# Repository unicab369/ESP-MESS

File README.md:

# What is it?
ESP-MESS is an open-source firmware for ESP8266 and ESP32 microcontrollers, enabling\
rapid IoT prototyping for home automation, smart farming, smart business, and more. 

## Why ESP-Mess? 
Back in 2020 during Covid, I got an opportunity to look back and decide on what I want to do next. I thought about what I liked as a kid so I decided to build a remote control car. During my search for a suitable microcontroller, I stumbled upon the NodeMcu, a development board that house the ESP8266 module. Initially underestimating its capabilities, I soon realized its potential. Since then, my journey has led me to acquire skills in soldering, basic electronics, embedded programming, web development for microcontrollers, PCB design, and various wireless communication technologies.

I am building a Wireless Bridge System that can manage multiple devices using a variety of wireless technologies. The system is designed to be flexible and scalable, allowing it to adapt to different wireless application requirements. My goal is to explore and discover different IoT applications while keeping the cost minimal. To achieve this, I created ESP-MESS.

## Why a Wireless Bridge System (WBSys)?
Because it's cool. It's very cool. Ok, seriously, different wireless technologies have their own unique advantages and disadvantages. For instance, LoRa technology allows devices to communicate with each other over long distances, which is not possible with WiFi or Bluetooth. However, LoRa has a low data rate, which makes it unsuitable for transmitting large amounts of data such as videos or audios. On the other hand, UWB (Ultra Wide Band) technology has a short range but enables devices to be accurately positioned relative to another device. WiFi can stream a lot more data over the air compared to Bluetooth, but at the cost of higher power consumption, making it less suitable for battery-operated devices than Bluetooth or BLE. These are just a few examples of the advantages and disadvantages of different wireless technologies.

A Wireless Bridge System offers a versatile solution by allowing the integration of diverse wireless technologies to address various challenges. Users can enhance their networks by adding supported modules to the bridge, taking advantage of the strengths of each wireless technology. This flexibility empowers users to tailor custom wireless networks to fulfill specific needs, whether it's creating a wireless sensor network, a smart home automation system, a mesh network for industrial automation, or a communication system for autonomous vehicles. The system facilitates the extension, management, monitoring, and control of device networks. ESP-MESS is an implementation of this system, it offers carefully chosen supporting devices that balance performance and cost, enabling users to choose components that align with their requirements and budgets.

checkout our discord channel: 
https://discord.com/channels/793348436475904022/858758498875342878

A Live ESP-MESS Node:
This is an ESP-MESS Node that runs on a Lithium-ion 18650 battery and a solar panel. The device records the temperature, humidity, ambient light level, battery voltage level, and the charging current from a solar panel. It utilizes ESP-Now to send signals to another Node, which is connected to my WiFi network. This Node publishes the readings to IoTPlotter for storage and data analysis.
https://iotplotter.com/user/feed/627987619219815565

### A Solar Node

### Data visualization

<br>

# What is the vision?
### Below is the rough draft of the initial vision. Please excuse my English.

### An example a configuration

# what is the state of the project?
Right now it's functional but I have not finished document the setup. 
I will try to make a video with instructions on how to work it.

Currently I have got ESP-Now working and some works for the LoRa communication has been completed.
Next step is to refine the ESP-Now, LoRa, and then add support for BLE.

### What am I working on right now?
Currently, I'm testing a few BLE modules. I'm trying to measure the power consumption of different devices and compare them with each other. This way I can pick one that I think is best suited for a low power device that can monitor multiple sensor nodes and can last on a battery for the minimum of 1 year.

make all monitor

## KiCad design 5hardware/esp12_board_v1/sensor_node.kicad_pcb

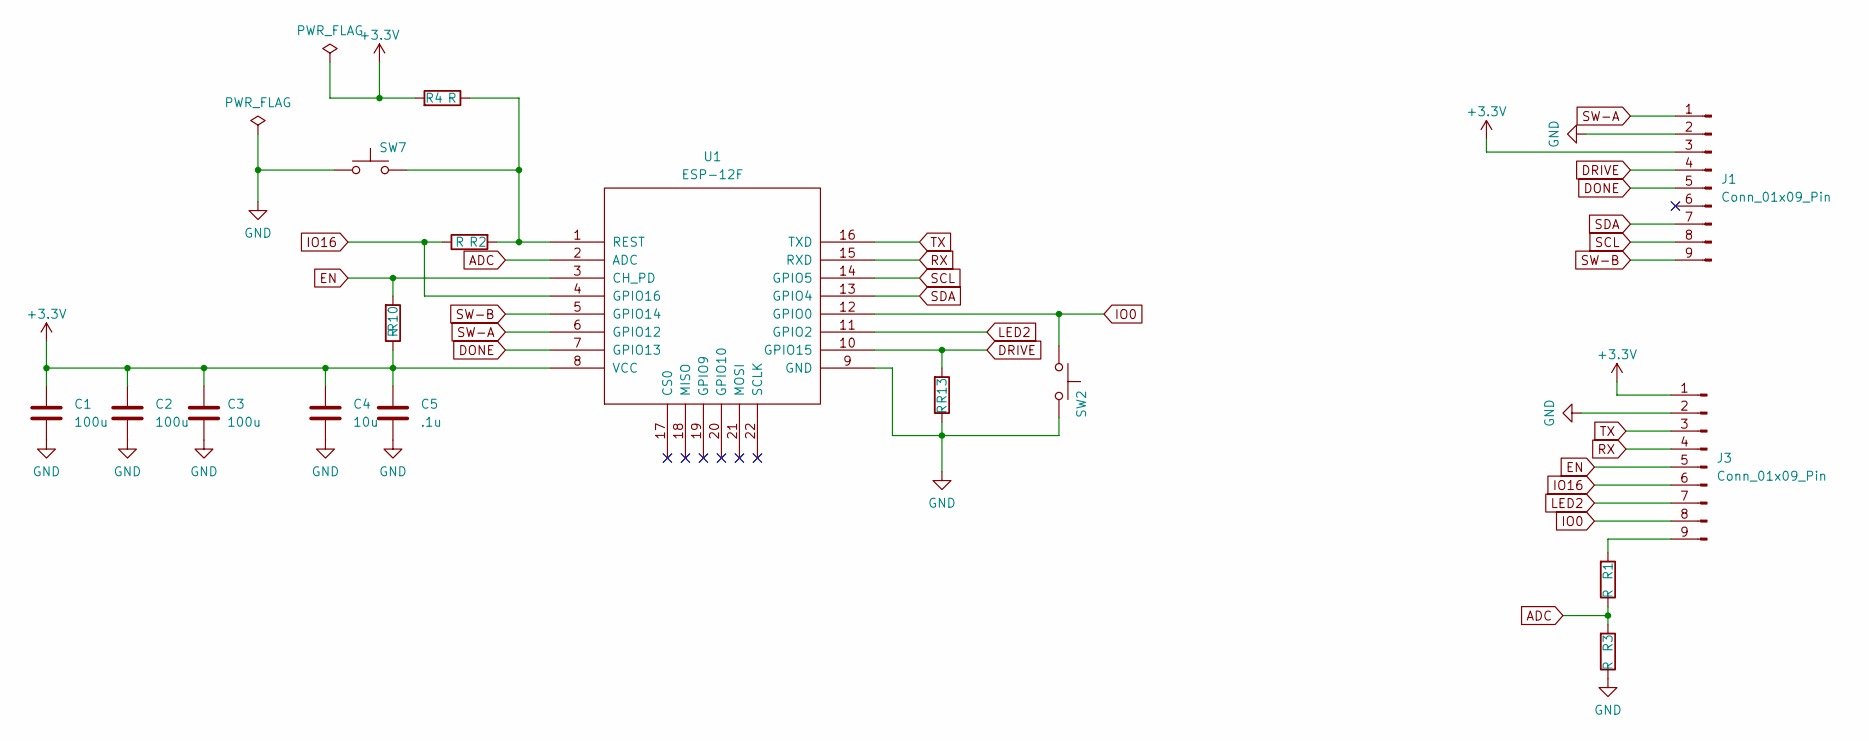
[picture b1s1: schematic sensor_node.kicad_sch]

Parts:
C1, C2, C3: 100u; C_1206_3216Metric
C4: 10u; C_0603_1608Metric
C5: .1u; C_0603_1608Metric
J1, J3: Conn_01x09_Pin; PinHeader_1x09_P2.54mm_Vertical
R1, R3, R4, R10, R13: R; R_0603_1608Metric
R2: R; Jumpper
SW2, SW7: SW_Push; SW_SPST_PTS810
U1: ESP-12F; ESP12_SMD

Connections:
+3.3V: C1.1, C2.1, C3.1, C4.1, C5.1, J1.3, J3.1, R4.2, R10.1, U1.8 (VCC)
ADC: R1.1, R3.2, U1.2 (ADC)
DONE: J1.5, U1.7 (GPIO13)
DRIVE: J1.4, R13.2, U1.10 (GPIO15)
EN: J3.5, R10.2, U1.3 (CH_PD)
GND: C1.2, C2.2, C3.2, C4.2, C5.2, J1.2, J3.2, R3.1, R13.1, SW2.1, SW7.2, U1.9 (GND)
IO0: J3.8, SW2.2, U1.12 (GPIO0)
IO16: J3.6, R2.1, U1.4 (GPIO16)
LED2: J3.7, U1.11 (GPIO2)
unnamed: J3.9, R1.2
unnamed: R2.2, R4.1, SW7.1, U1.1 (REST)
RX: J3.4, U1.15 (RXD)
SCL: J1.8, U1.14 (GPIO5)
SDA: J1.7, U1.13 (GPIO4)
SW-A: J1.1, U1.6 (GPIO12)
SW-B: J1.9, U1.5 (GPIO14)
TX: J3.3, U1.16 (TXD)

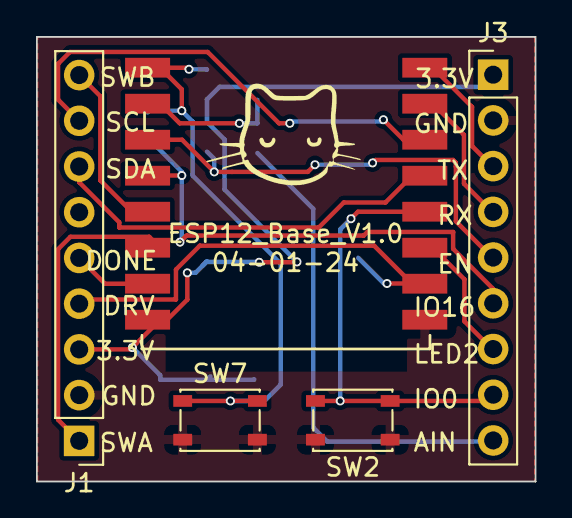
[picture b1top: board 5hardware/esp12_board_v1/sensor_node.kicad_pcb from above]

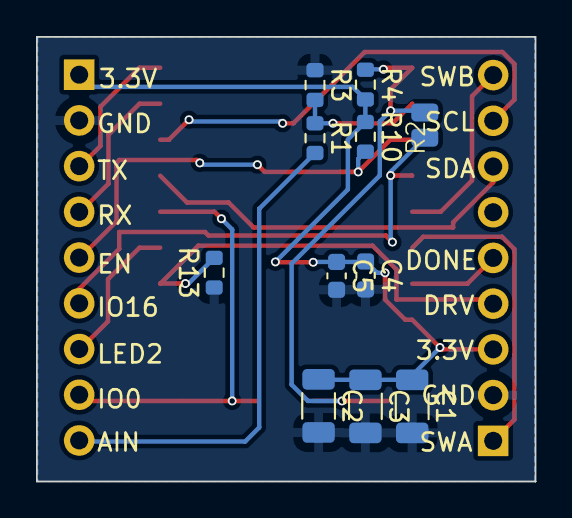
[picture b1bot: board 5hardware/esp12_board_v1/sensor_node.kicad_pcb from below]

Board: 2 copper layers, 27.7 x 24.7 mm, 16 parts (11 on the bottom side), 17 nets.

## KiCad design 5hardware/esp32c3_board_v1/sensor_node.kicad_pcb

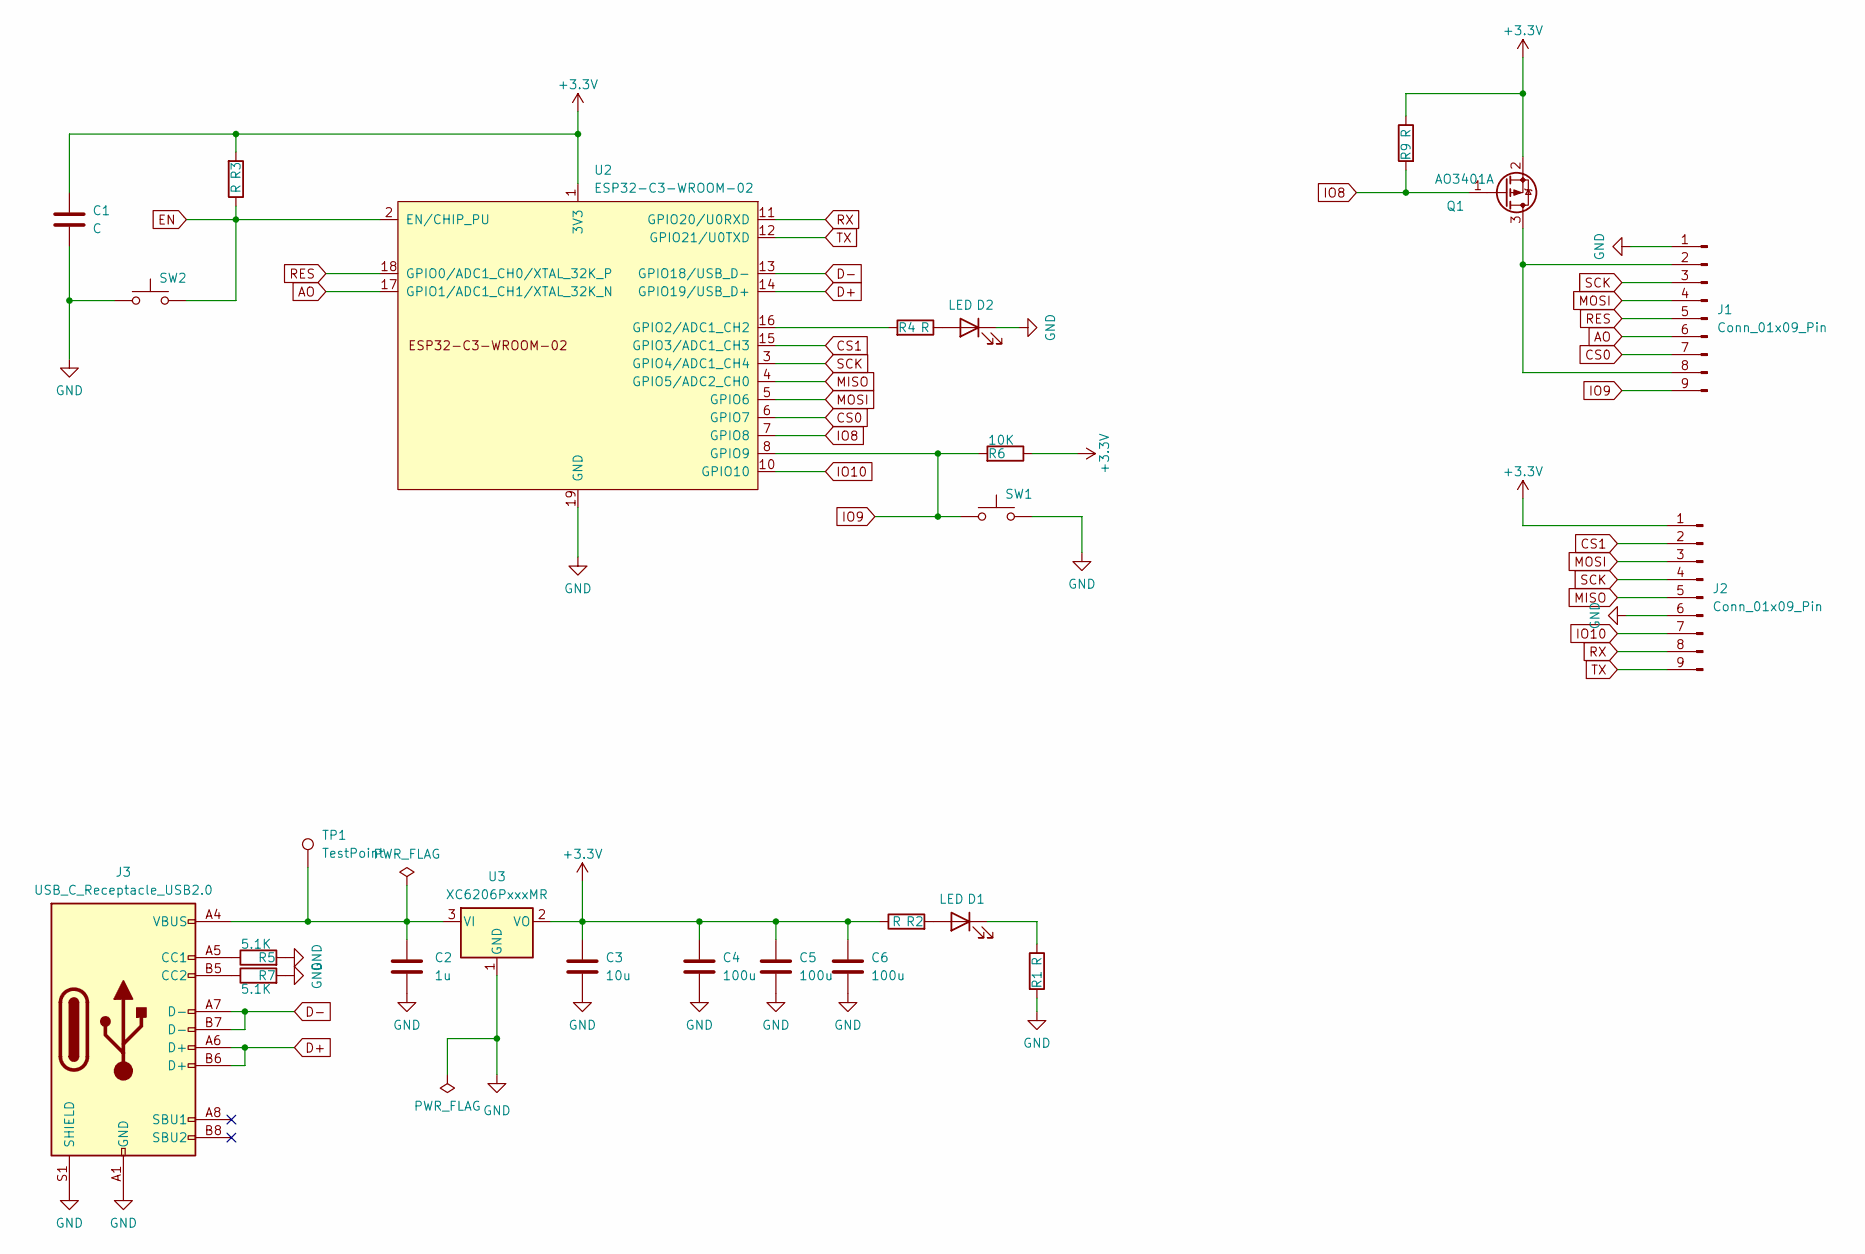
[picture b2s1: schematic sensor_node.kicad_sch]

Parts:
C1: C; C_0603_1608Metric
C2: 1u; C_0603_1608Metric
C3: 10u; C_0603_1608Metric
C4, C5, C6: 100u; C_1206_3216Metric
D1, D2: LED; LED_0603_1608Metric
J1, J2: Conn_01x09_Pin; PinHeader_1x09_P2.54mm_Vertical
J3: USB_C_Receptacle_USB2.0; USB_C_Receptacle_HRO_TYPE-C-31-M-12
Q1: AO3401A; SOT-23
R1: R; Jumpper
R2, R3, R4, R9: R; R_0603_1608Metric
R5, R7: 5.1K; R_0603_1608Metric
R6: 10K; R_0603_1608Metric
SW1, SW2: SW_Push; SW_SPST_PTS810
TP1: TestPoint; testpoint
U2: ESP32-C3-WROOM-02; MODULE_ESP32-C3-WROOM-02-H4
U3: XC6206PxxxMR; SOT-23-3

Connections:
+3.3V: C1.1, C3.1, C4.1, C5.1, C6.1, J2.1, Q1.2 (S), R2.1, R3.2, R6.1, R9.1, U2.1 (3V3), U3.2 (VO)
AO: J1.6, U2.17 (GPIO1/ADC1_CH1/XTAL_32K_N)
CS0: J1.7, U2.6 (GPIO7)
CS1: J2.2, U2.15 (GPIO3/ADC1_CH3)
D+: J3.A6 (D+), J3.B6 (D+), U2.14 (GPIO19/USB_D+)
D-: J3.A7 (D-), J3.B7 (D-), U2.13 (GPIO18/USB_D-)
EN: R3.1, SW2.1, U2.2 (EN/CHIP_PU)
GND: C1.2, C2.2, C3.2, C4.2, C5.2, C6.2, D2.1 (K), J1.1, J2.6, J3.A1 (GND), J3.A12 (GND), J3.B1 (GND), J3.B12 (GND), J3.S1 (SHIELD), R1.2, R5.2, R7.2, SW1.1, SW2.2, U2.9 (GND), U2.19 (GND), U3.1 (GND)
IO8: Q1.1 (G), R9.2, U2.7 (GPIO8)
IO9: J1.9, R6.2, SW1.2, U2.8 (GPIO9)
IO10: J2.7, U2.10 (GPIO10)
MISO: J2.5, U2.4 (GPIO5/ADC2_CH0)
MOSI: J1.4, J2.3, U2.5 (GPIO6)
unnamed: D1.2 (A), R2.2
unnamed: D1.1 (K), R1.1
unnamed: D2.2 (A), R4.1
unnamed: J1.2, J1.8, Q1.3 (D)
unnamed: J3.A5 (CC1), R5.1
unnamed: J3.B5 (CC2), R7.1
unnamed: R4.2, U2.16 (GPIO2/ADC1_CH2)
unnamed: C2.1, J3.A4 (VBUS), J3.A9 (VBUS), J3.B4 (VBUS), J3.B9 (VBUS), TP1.1, U3.3 (VI)
RES: J1.5, U2.18 (GPIO0/ADC1_CH0/XTAL_32K_P)
RX: J2.8, U2.11 (GPIO20/U0RXD)
SCK: J1.3, J2.4, U2.3 (GPIO4/ADC1_CH4)
TX: J2.9, U2.12 (GPIO21/U0TXD)

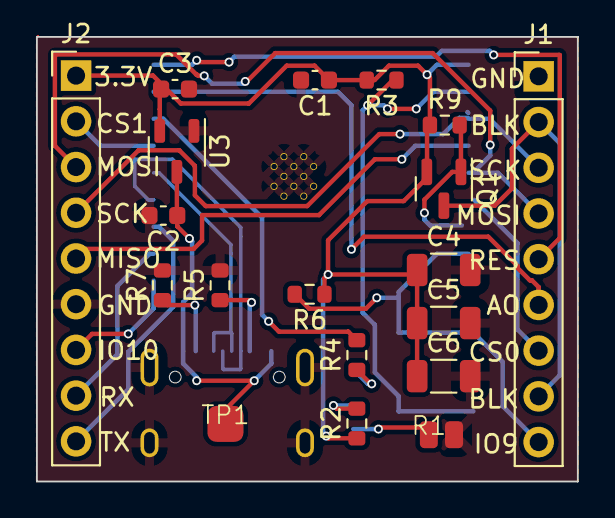
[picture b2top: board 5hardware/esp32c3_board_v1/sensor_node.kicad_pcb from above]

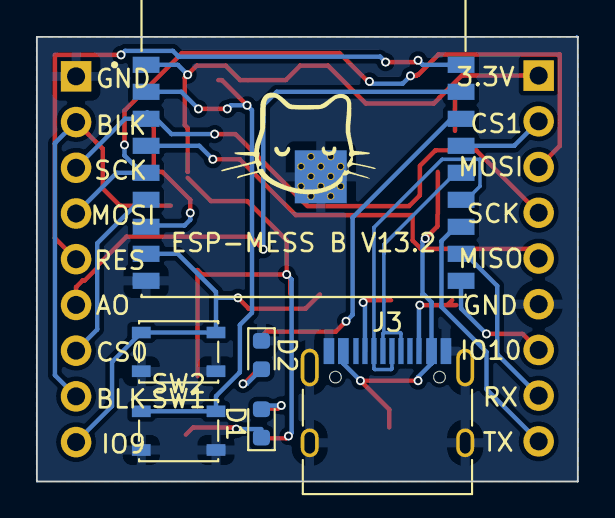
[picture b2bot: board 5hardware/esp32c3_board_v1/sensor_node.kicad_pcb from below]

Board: 2 copper layers, 30.1 x 24.7 mm, 25 parts (6 on the bottom side), 25 nets.

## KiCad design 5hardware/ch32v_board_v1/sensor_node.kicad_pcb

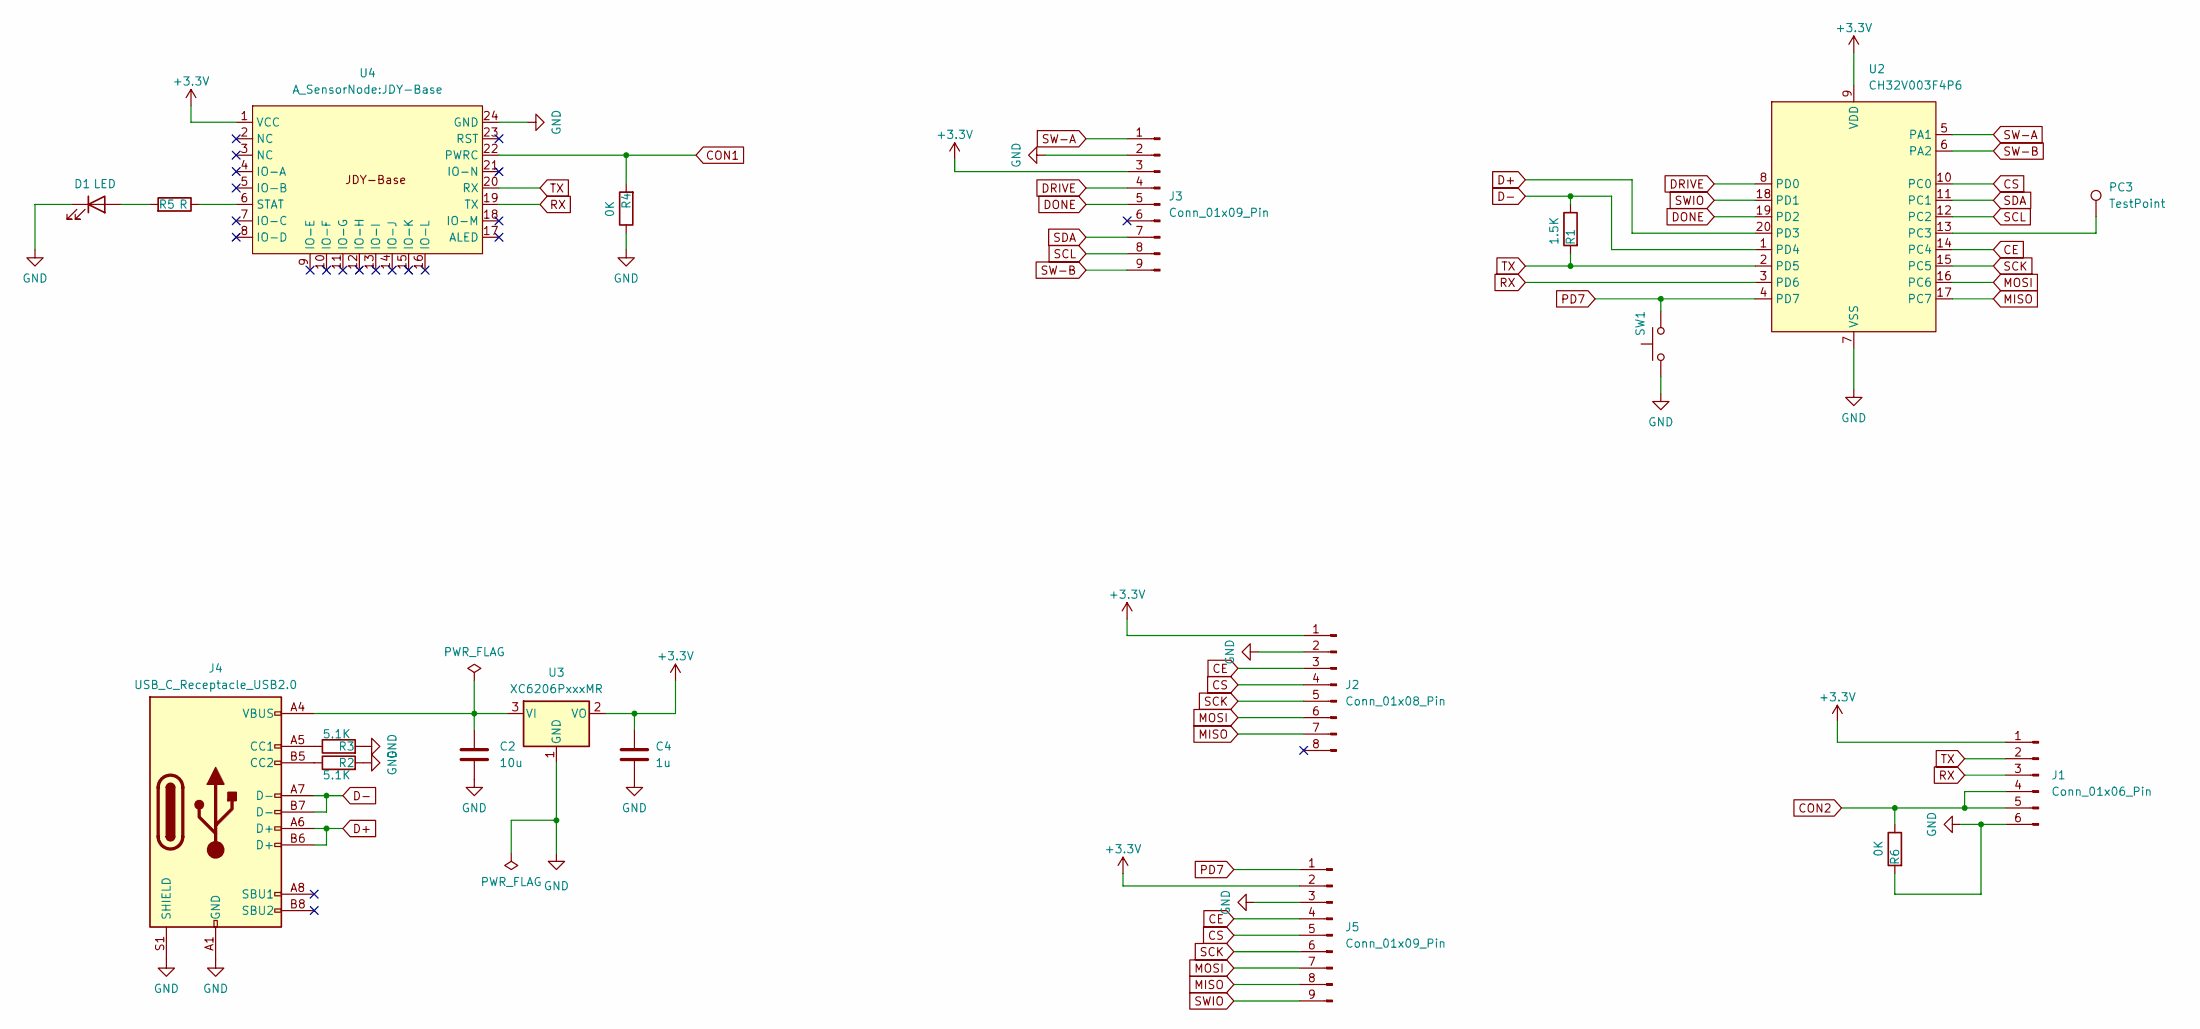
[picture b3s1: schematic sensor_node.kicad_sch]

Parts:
C2: 10u; C_0603_1608Metric
C4: 1u; C_0603_1608Metric
D1: LED; LED_0603_1608Metric
J1: Conn_01x06_Pin; JDY-41
J2: Conn_01x08_Pin; Nrf24L01
J3, J5: Conn_01x09_Pin; PinHeader_1x09_P2.54mm_Vertical
J4: USB_C_Receptacle_USB2.0; USB_C_Receptacle_HRO_TYPE-C-31-M-12
PC3: TestPoint; testpoint
R1: 1.5K; R_0603_1608Metric
R2, R3: 5.1K; R_0603_1608Metric
R4, R6: 0K; Jumpper
R5: R; R_0603_1608Metric
SW1: SW_Push; SW_SPST_PTS810
U2: CH32V003F4P6; TSSOP-20_4.4x6.5mm_P0.65mm
U3: XC6206PxxxMR; SOT-23-3
U4: JDY-Base

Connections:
+3.3V: C4.1, J1.1, J2.1, J3.3, J5.2, U2.9 (VDD), U3.2 (VO), U4.1 (VCC)
CE: J2.3, J5.4, U2.14 (PC4)
CON1: R4.2, U4.22 (PWRC)
CON2: J1.4, J1.5, R6.1
CS: J2.4, J5.5, U2.10 (PC0)
D+: J4.A6 (D+), J4.B6 (D+), U2.20 (PD3)
D-: J4.A7 (D-), J4.B7 (D-), R1.1, U2.1 (PD4)
DONE: J3.5, U2.19 (PD2)
DRIVE: J3.4, U2.8 (PD0)
GND: C2.2, C4.2, D1.1 (K), J1.6, J2.2, J3.2, J4.A1 (GND), J4.A12 (GND), J4.B1 (GND), J4.B12 (GND), J4.S1 (SHIELD), J5.3, R2.2, R3.2, R4.1, R6.2, SW1.2, U2.7 (VSS), U3.1 (GND), U4.24 (GND)
MISO: J2.7, J5.8, U2.17 (PC7)
MOSI: J2.6, J5.7, U2.16 (PC6)
unnamed: D1.2 (A), R5.2
unnamed: J4.A5 (CC1), R3.1
unnamed: J4.B5 (CC2), R2.1
unnamed: PC3.1, U2.13 (PC3)
unnamed: C2.1, J4.A4 (VBUS), J4.A9 (VBUS), J4.B4 (VBUS), J4.B9 (VBUS), U3.3 (VI)
unnamed: R5.1, U4.6 (STAT)
PD7: J5.1, SW1.1, U2.4 (PD7)
RX: J1.3, U2.3 (PD6), U4.19 (TX)
SCK: J2.5, J5.6, U2.15 (PC5)
SCL: J3.8, U2.12 (PC2)
SDA: J3.7, U2.11 (PC1)
SW-A: J3.1, U2.5 (PA1)
SW-B: J3.9, U2.6 (PA2)
SWIO: J5.9, U2.18 (PD1)
TX: J1.2, R1.2, U2.2 (PD5), U4.20 (RX)

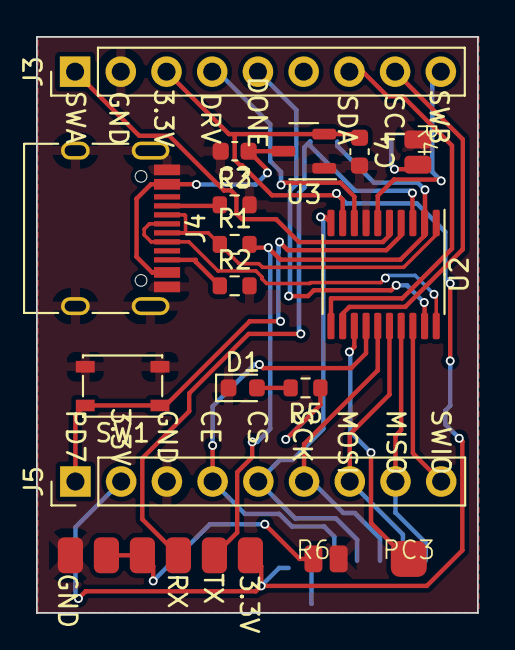
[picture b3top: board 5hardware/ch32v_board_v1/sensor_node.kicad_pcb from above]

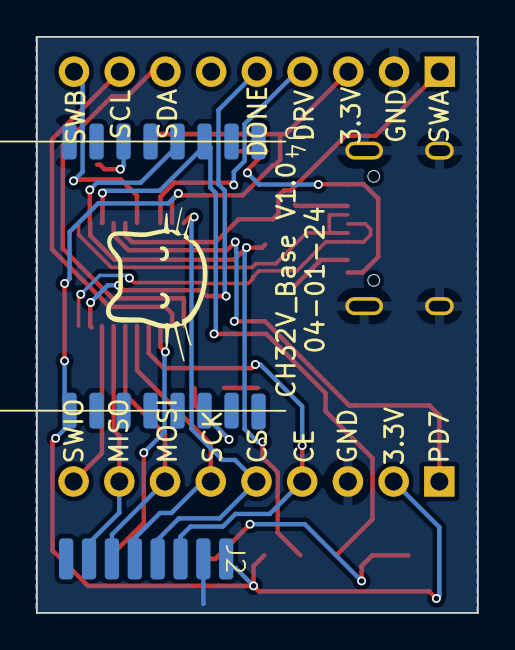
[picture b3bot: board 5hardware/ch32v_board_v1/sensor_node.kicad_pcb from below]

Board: 2 copper layers, 24.5 x 32.0 mm, 19 parts (2 on the bottom side), 27 nets.

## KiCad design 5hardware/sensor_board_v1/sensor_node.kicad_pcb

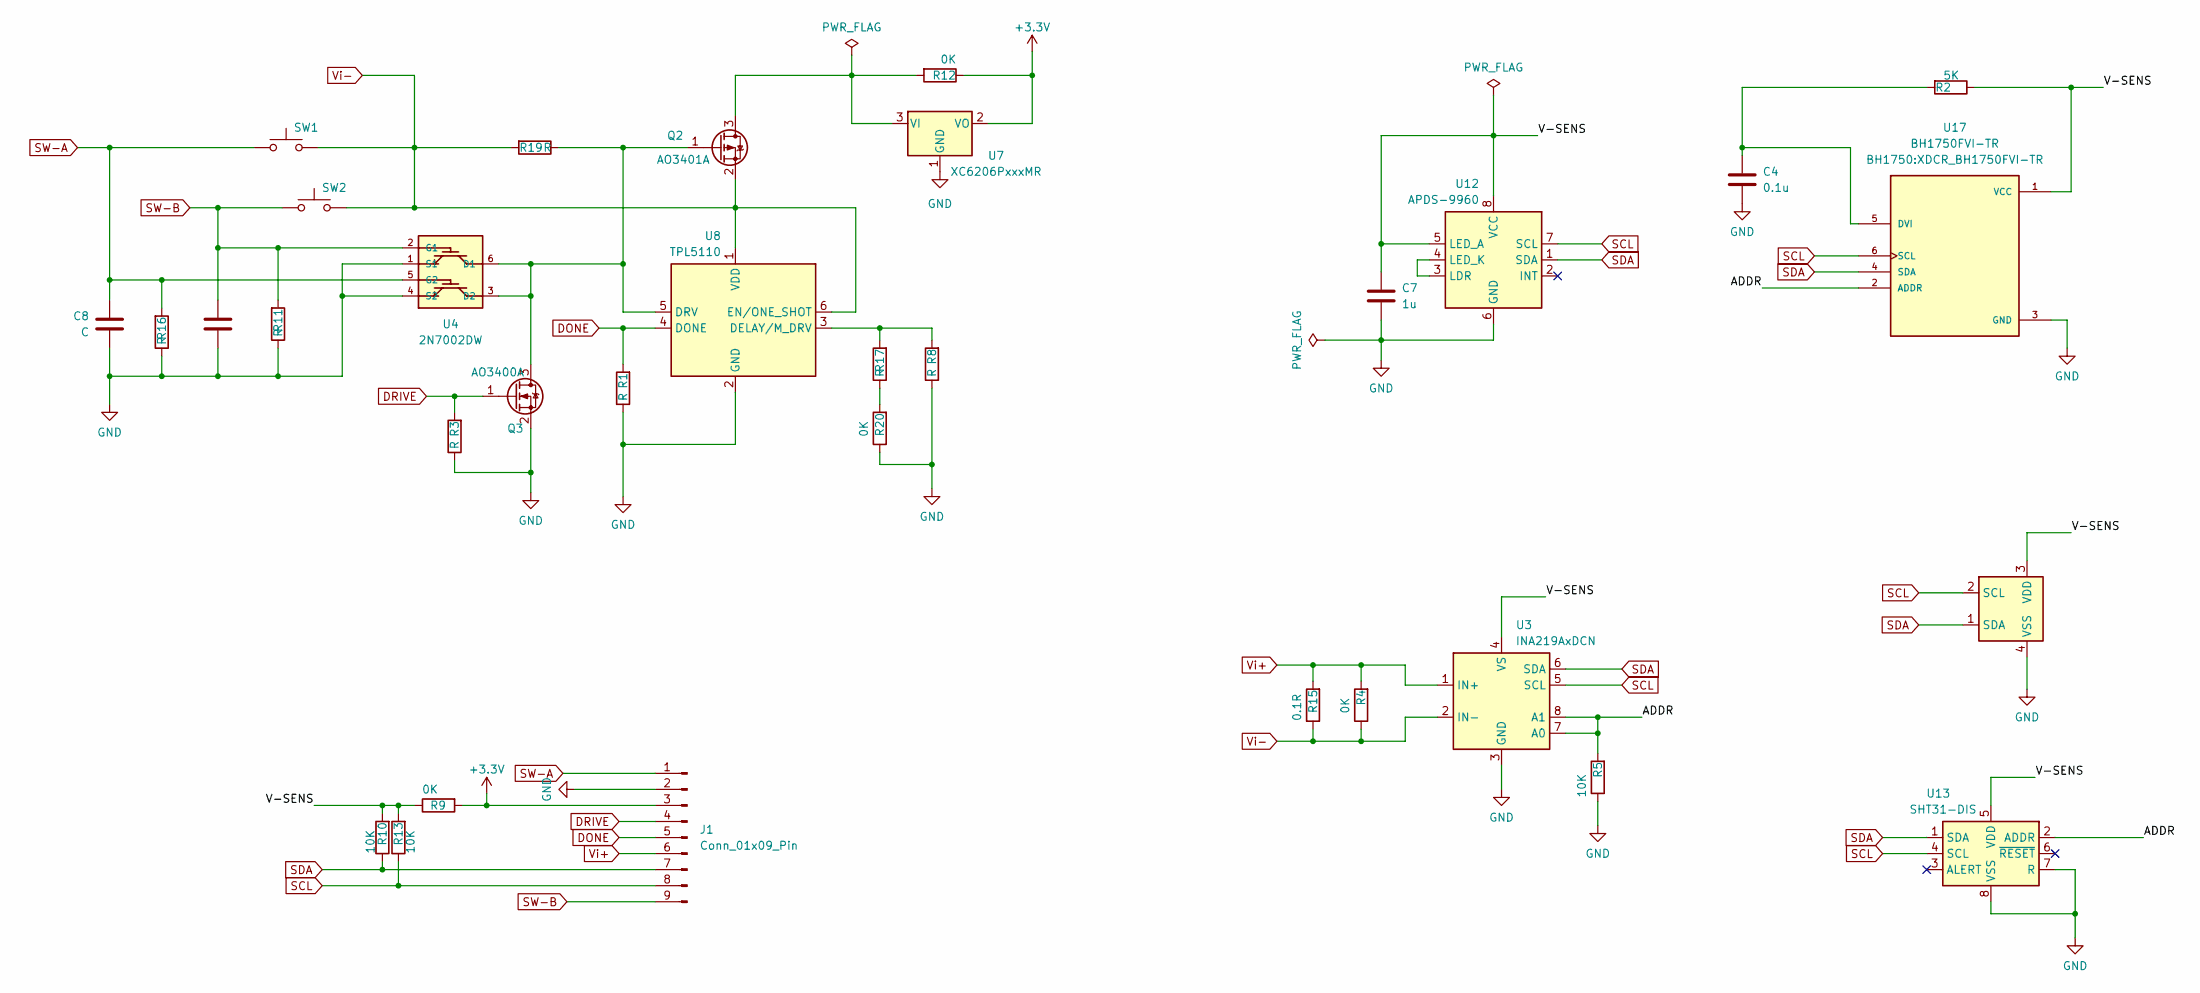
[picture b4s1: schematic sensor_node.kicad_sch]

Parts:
C2, C8: C; C_0603_1608Metric
C4: 0.1u; C_0603_1608Metric
C7: 1u; C_0603_1608Metric
J1: Conn_01x09_Pin; PinHeader_1x09_P2.54mm_Vertical
Q2: AO3401A; SOT-23
Q3: AO3400A; SOT-23
R1, R3, R8, R11, R16, R17, R19: R; R_0603_1608Metric
R2: 5K; R_0603_1608Metric
R4, R9, R12, R20: 0K; Jumpper
R5, R10, R13: 10K; R_0603_1608Metric
R15: 0.1R; R_2512_6332Metric
SW1, SW2: SW_Push; SW_SPST_PTS810
U1: SHT4x; Sensirion_DFN-4_1.5x1.5mm_P0.8mm_SHT4x_NoCentralPad
U3: INA219AxDCN; SOT-23-8
U4: 2N7002DW; SOT363
U7: XC6206PxxxMR; SOT-23-3
U8: TPL5110; SOT-23-6
U12: APDS-9960; Avago_APDS-9960
U13: SHT31-DIS; Sensirion_DFN-8-1EP_2.5x2.5mm_P0.5mm_EP1.1x1.7mm
U17: BH1750FVI-TR; XDCR_BH1750FVI-TR; PARTREV D

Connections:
+3.3V: J1.3, R9.2, R12.1, U7.2 (VO)
/ADDR: R5.2, U3.7 (A0), U3.8 (A1), U13.2 (ADDR), U17.2 (ADDR)
/V-SENS: C7.1, R2.1, R9.1, R10.2, R13.2, U1.3 (VDD), U3.4 (VS), U12.5 (LED_A), U12.8 (VCC), U13.5 (VDD), U17.1 (VCC)
DONE: J1.5, R1.2, U8.4 (DONE)
DRIVE: J1.4, Q3.1 (G), R3.2
GND: C2.2, C4.2, C7.2, C8.2, J1.2, Q3.2 (S), R1.1, R3.1, R5.1, R8.1, R11.1, R16.1, R20.1, U1.4 (VSS), U3.3 (GND), U4.1 (S1), U4.4 (S2), U7.1 (GND), U8.2 (GND), U12.6 (GND), U13.7 (R), U13.8 (VSS), U13.9 (VSS), U17.3 (GND)
unnamed: Q2.3 (D), R12.2, U7.3 (VI)
unnamed: Q2.1 (G), Q3.3 (D), R19.1, U4.3 (D2), U4.6 (D1), U8.5 (DRV)
unnamed: R17.1, R20.2
unnamed: R8.2, R17.2, U8.3 (DELAY/M_DRV)
unnamed: U12.3 (LDR), U12.4 (LED_K)
unnamed: C4.1, R2.2, U17.5 (DVI)
SCL: J1.8, R13.1, U1.2 (SCL), U3.5 (SCL), U12.7 (SCL), U13.4 (SCL), U17.6 (SCL)
SDA: J1.7, R10.1, U1.1 (SDA), U3.6 (SDA), U12.1 (SDA), U13.1 (SDA), U17.4 (SDA)
SW-A: C8.1, J1.1, R16.2, SW1.2, U4.5 (G2)
SW-B: C2.1, J1.9, R11.2, SW2.2, U4.2 (G1)
Vi+: J1.6, R4.2, R15.2, U3.1 (IN+)
Vi-: Q2.2 (S), R4.1, R15.1, R19.2, SW1.1, SW2.1, U3.2 (IN-), U8.1 (VDD), U8.6 (EN/ONE_SHOT)

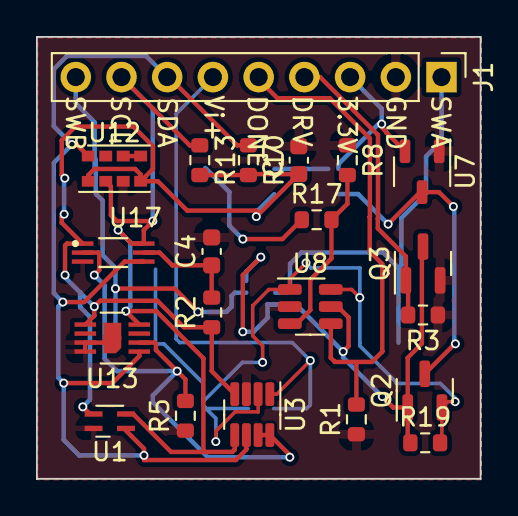
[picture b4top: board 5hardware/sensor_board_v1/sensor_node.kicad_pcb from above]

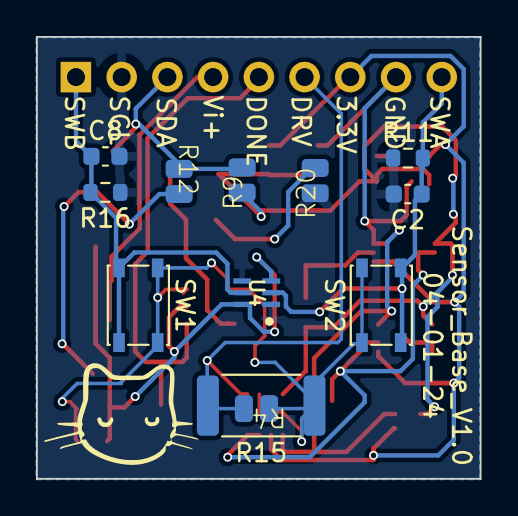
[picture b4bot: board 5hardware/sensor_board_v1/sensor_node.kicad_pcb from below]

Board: 2 copper layers, 24.7 x 24.6 mm, 33 parts (12 on the bottom side), 18 nets.

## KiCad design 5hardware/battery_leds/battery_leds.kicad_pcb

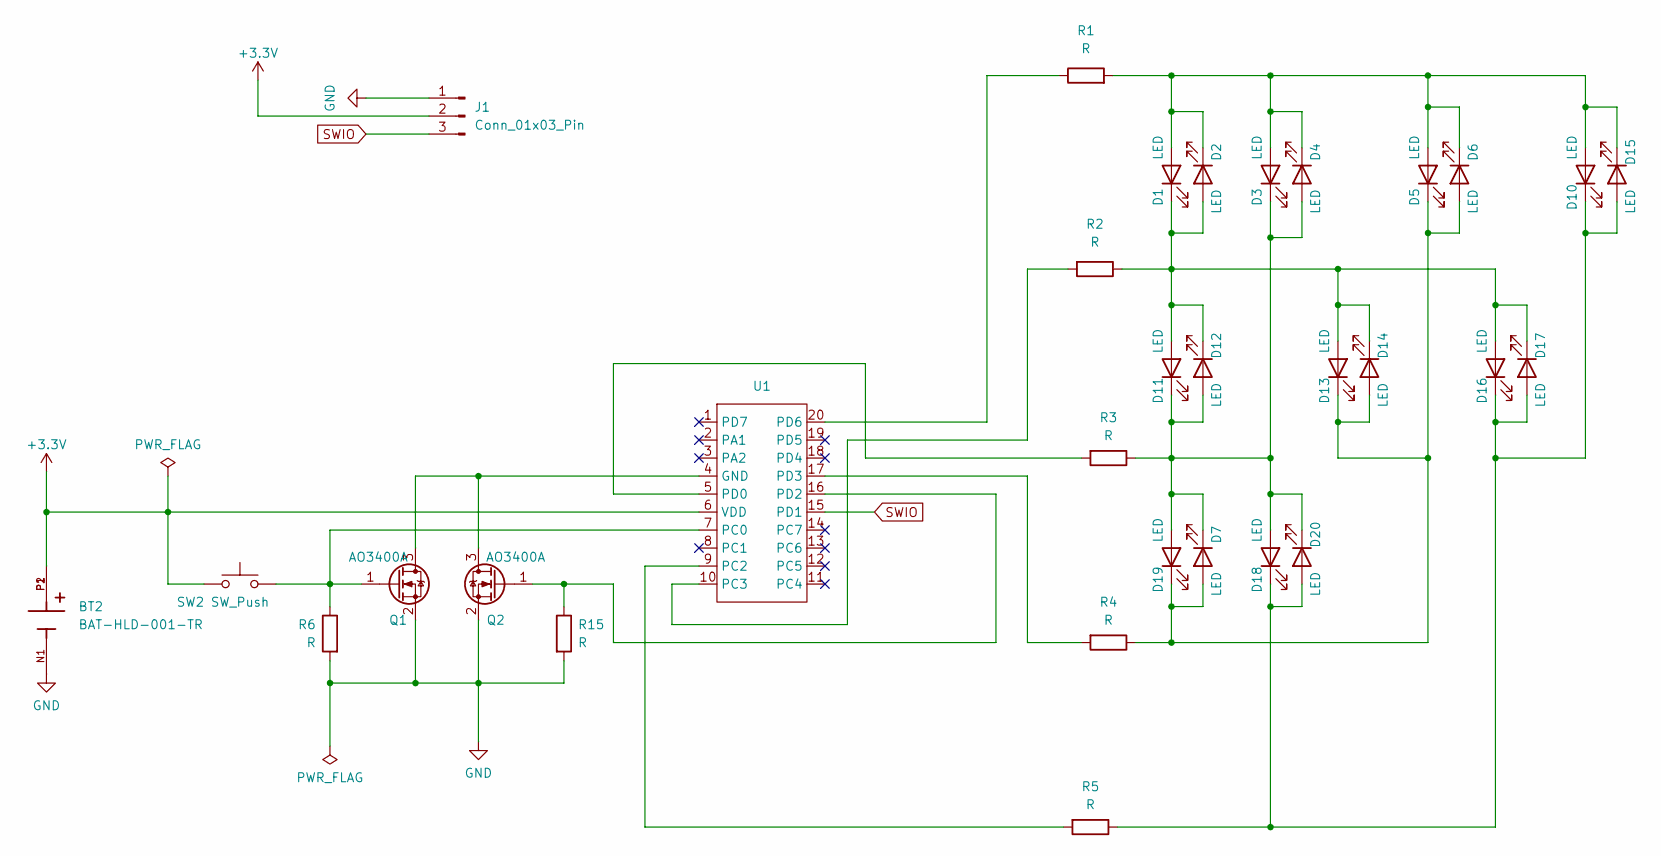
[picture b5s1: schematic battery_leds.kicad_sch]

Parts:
BT2: BAT-HLD-001-TR; BAT_BAT-HLD-001-TR; PARTREV B
D1, D2, D3, D4, D5, D6, D7, D10, D11, D12, D13, D14, D15, D16, D17, D18, D19, D20: LED; LED_0603_1608Metric
J1: Conn_01x03_Pin; PinHeader_1x03_P2.00mm_Vertical
Q1, Q2: AO3400A; SOT-23
R1, R2, R3, R4, R5, R6, R15: R; R_0603_1608Metric
SW2: SW_Push; SW_SPST_PTS810
U1: QFN-20-1EP_3x3mm_P0.4mm_EP1.65x1.65mm

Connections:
+3.3V: BT2.P1, BT2.P2, J1.2, SW2.2, U1.6 (VDD)
GND: BT2.N1, J1.1, Q1.2 (S), Q2.2 (S), R6.2, R15.2
unnamed: D1.2 (A), D2.1 (K), D3.2 (A), D4.1 (K), D5.2 (A), D6.1 (K), D10.2 (A), D15.1 (K), R1.2
unnamed: D1.1 (K), D2.2 (A), D11.2 (A), D12.1 (K), D13.2 (A), D14.1 (K), D16.2 (A), D17.1 (K), R2.1
unnamed: D10.1 (K), D15.2 (A), D16.1 (K), D17.2 (A), D18.1 (K), D20.2 (A), R5.1
unnamed: D3.1 (K), D4.2 (A), D7.1 (K), D11.1 (K), D12.2 (A), D18.2 (A), D19.2 (A), D20.1 (K), R3.1
unnamed: D5.1 (K), D6.2 (A), D7.2 (A), D13.1 (K), D14.2 (A), D19.1 (K), R4.1
unnamed: Q1.3 (D), Q2.3 (D), U1.4 (GND)
unnamed: Q1.1 (G), R6.1, SW2.1, U1.7 (PC0)
unnamed: Q2.1 (G), R15.1, U1.16 (PD2)
unnamed: R5.2, U1.9 (PC2)
unnamed: R2.2, U1.10 (PC3)
unnamed: R3.2, U1.5 (PD0)
unnamed: R4.2, U1.17 (PD3)
unnamed: R1.1, U1.20 (PD6)
SWIO: J1.3, U1.15 (PD1)

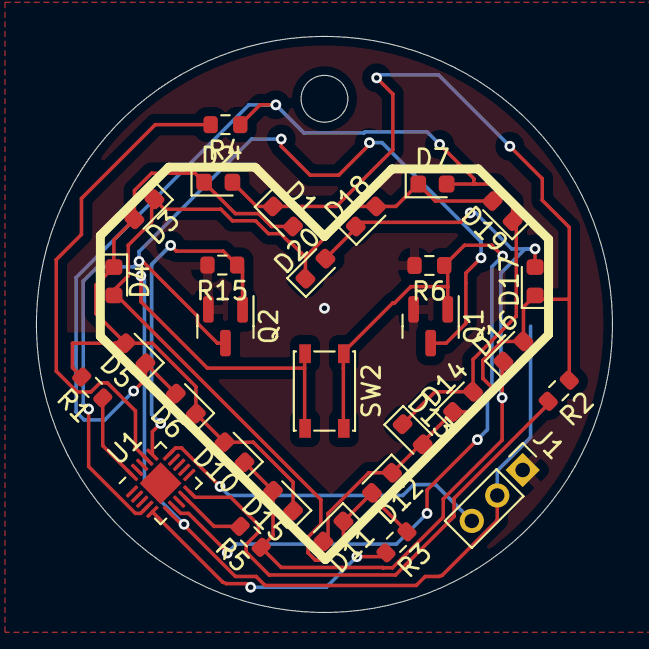
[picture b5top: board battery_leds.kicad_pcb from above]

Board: 2 copper layers, 32.0 x 32.0 mm, 31 parts (1 on the bottom side), 16 nets.

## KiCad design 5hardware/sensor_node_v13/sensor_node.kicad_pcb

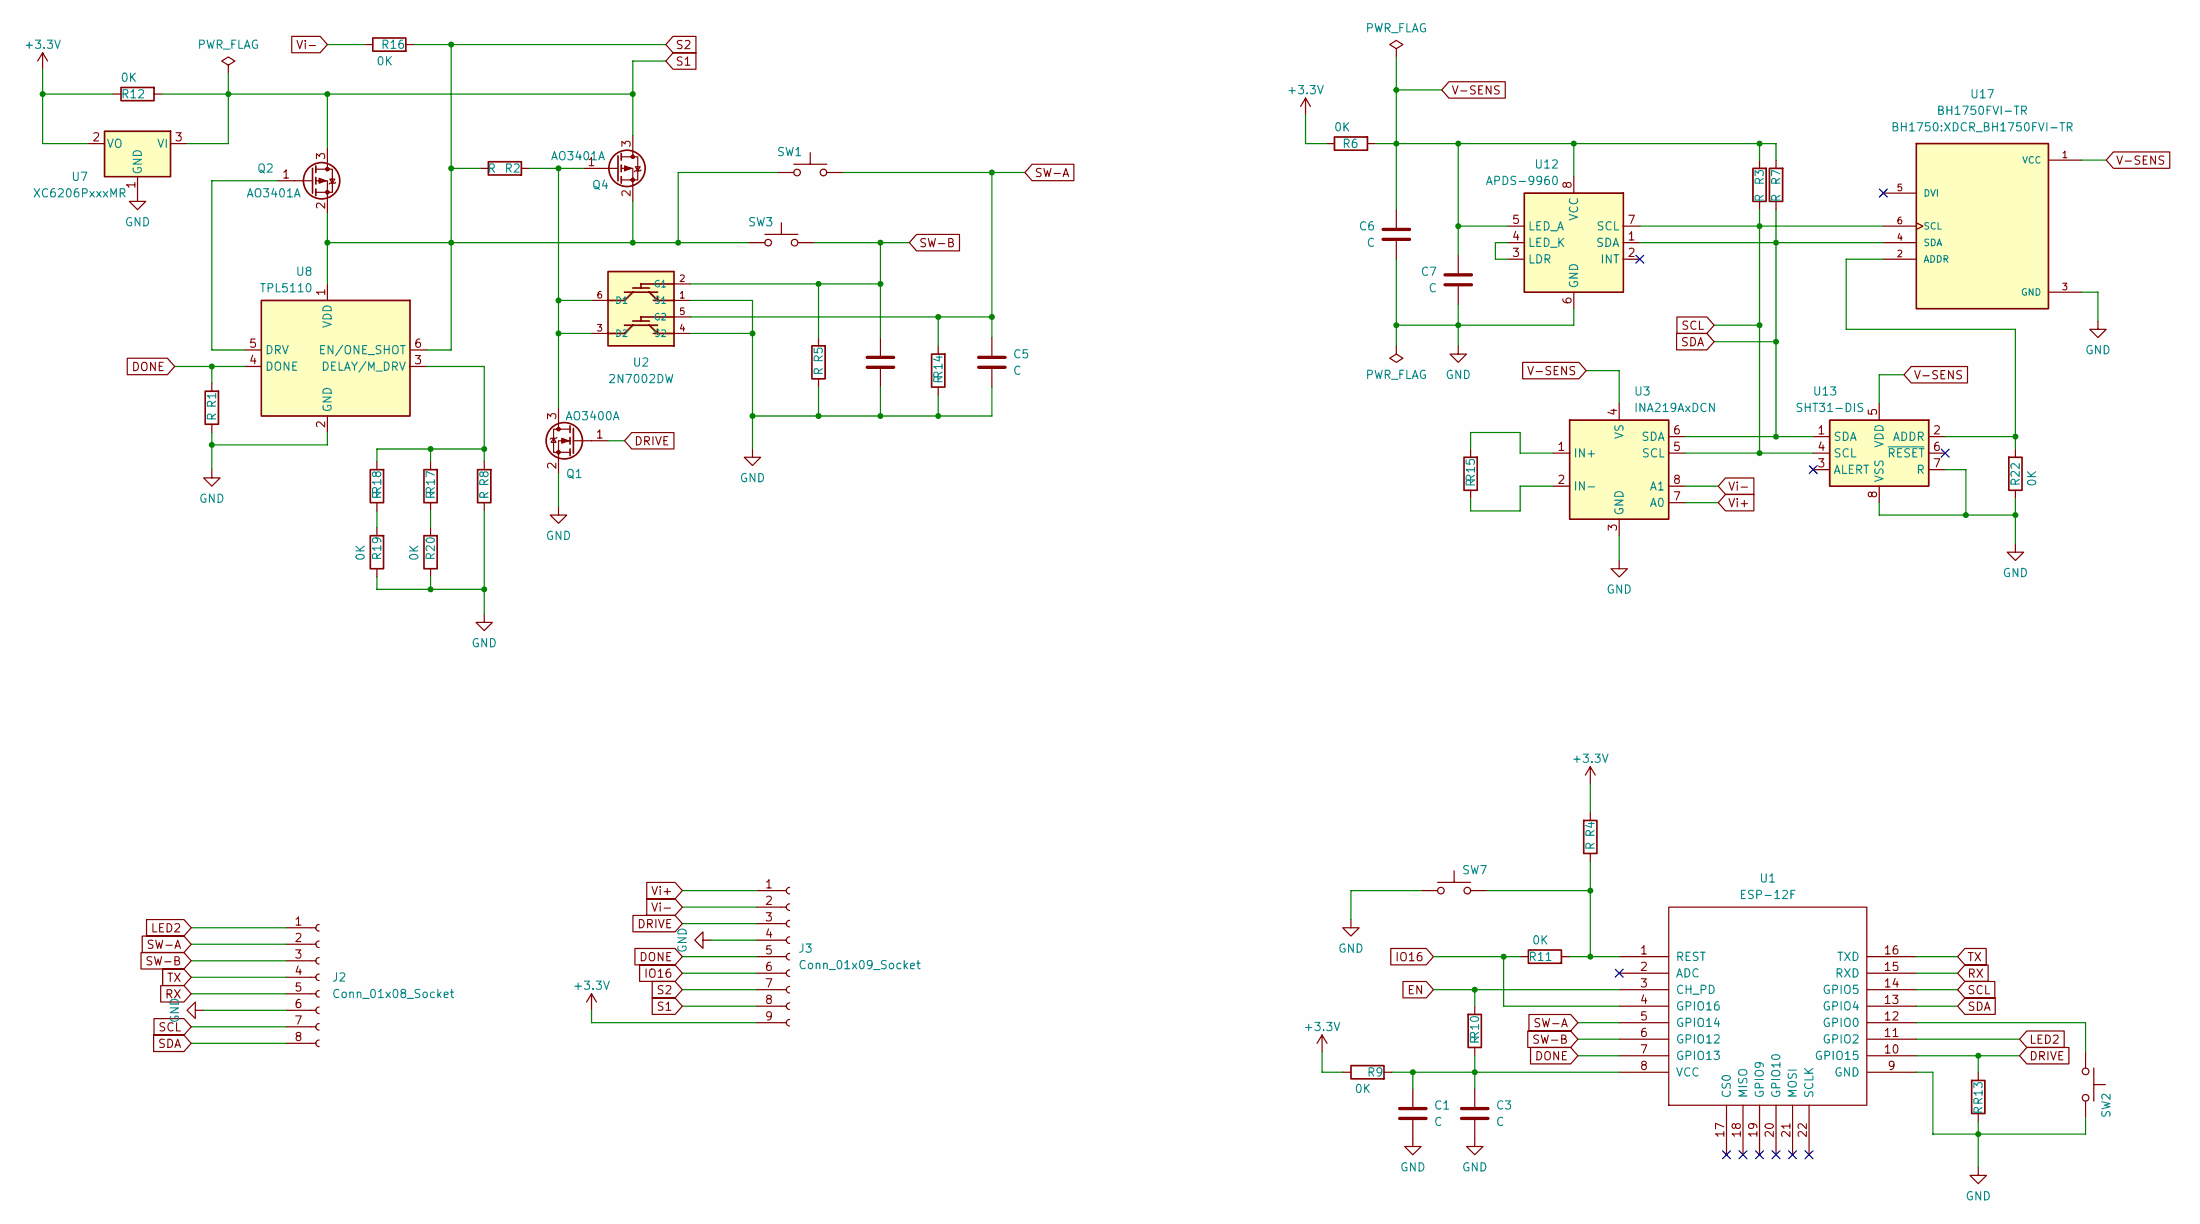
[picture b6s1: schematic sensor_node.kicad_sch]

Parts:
C1, C3, C4, C5, C6, C7: C; C_0603_1608Metric
J2: Conn_01x08_Socket; PinSocket_1x08_P2.54mm_Vertical
J3: Conn_01x09_Socket; PinSocket_1x09_P2.54mm_Vertical
Q1: AO3400A; SOT-23
Q2, Q4: AO3401A; SOT-23
R1, R2, R3, R4, R5, R7, R8, R10, R13, R14, R17, R18: R; R_0603_1608Metric
R6, R9, R11, R12, R16, R19, R20: 0K; R_0402_1005Metric
R15: R; R_2512_6332Metric
R22: 0K; R_0603_1608Metric
SW1, SW3: SW_Push; ButtonSwitch12mm_SMD
SW2, SW7: SW_Push; SW_SPST_PTS810
U1: ESP-12F; ESP12_SMD
U2: 2N7002DW; SOT363
U3: INA219AxDCN; SOT-23-8
U7: XC6206PxxxMR; SOT-23-3
U8: TPL5110; SOT-23-6
U12: APDS-9960; Avago_APDS-9960
U13: SHT31-DIS; Sensirion_DFN-8-1EP_2.5x2.5mm_P0.5mm_EP1.1x1.7mm
U17: BH1750FVI-TR; XDCR_BH1750FVI-TR; PARTREV D

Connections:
+3.3V: J3.9, R4.2, R6.1, R9.1, R12.1, U7.2 (VO)
DONE: J3.5, R1.2, U1.7 (GPIO13), U8.4 (DONE)
DRIVE: J3.3, Q1.1 (G), R13.2, U1.10 (GPIO15)
EN: R10.2, U1.3 (CH_PD)
GND: C1.2, C3.2, C4.2, C5.2, C6.2, C7.2, J2.6, J3.4, Q1.2 (S), R1.1, R5.1, R8.1, R13.1, R14.1, R19.1, R20.1, R22.1, SW2.1, SW7.2, U1.9 (GND), U2.1 (S1), U2.4 (S2), U3.3 (GND), U7.1 (GND), U8.2 (GND), U12.6 (GND), U13.7 (R), U13.8 (VSS), U13.9 (VSS), U17.3 (GND)
IO16: J3.6, R11.1, U1.4 (GPIO16)
LED2: J2.1, U1.11 (GPIO2)
unnamed: Q1.3 (D), Q4.1 (G), R2.2, U2.3 (D2), U2.6 (D1)
unnamed: Q2.1 (G), U8.5 (DRV)
unnamed: R17.1, R20.2
unnamed: R18.1, R19.2
unnamed: SW2.2, U1.12 (GPIO0)
unnamed: R4.1, R11.2, SW7.1, U1.1 (REST)
unnamed: C1.1, C3.1, R9.2, R10.1, U1.8 (VCC)
unnamed: R15.2, U3.1 (IN+)
unnamed: R15.1, U3.2 (IN-)
unnamed: R8.2, R17.2, R18.2, U8.3 (DELAY/M_DRV)
unnamed: U12.3 (LDR), U12.4 (LED_K)
unnamed: R22.2, U13.2 (ADDR), U17.2 (ADDR)
RX: J2.5, U1.15 (RXD)
S1: J3.8, Q2.3 (D), Q4.3 (D), R12.2, U7.3 (VI)
S2: J3.7, Q2.2 (S), Q4.2 (S), R2.1, R16.2, SW1.1, SW3.1, U8.1 (VDD), U8.6 (EN/ONE_SHOT)
SCL: J2.7, R3.1, U1.14 (GPIO5), U3.5 (SCL), U12.7 (SCL), U13.4 (SCL), U17.6 (SCL)
SDA: J2.8, R7.1, U1.13 (GPIO4), U3.6 (SDA), U12.1 (SDA), U13.1 (SDA), U17.4 (SDA)
SW-A: C5.1, J2.2, R14.2, SW1.2, U1.5 (GPIO14), U2.5 (G2)
SW-B: C4.1, J2.3, R5.2, SW3.2, U1.6 (GPIO12), U2.2 (G1)
TX: J2.4, U1.16 (TXD)
V-SENS: C6.1, C7.1, R3.2, R6.2, R7.2, U3.4 (VS), U12.5 (LED_A), U12.8 (VCC), U13.5 (VDD), U17.1 (VCC)
Vi+: J3.1, U3.7 (A0)
Vi-: J3.2, R16.1, U3.8 (A1)
